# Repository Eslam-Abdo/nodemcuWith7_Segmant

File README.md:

# Basic IoT project using ESP8266 (nodemcu) and microPython
### Requirement: 
change 7-segment's number using (Mobile app or hardware buttons) and display number on both (7-segment and mobile App) in real-time,
there are 3 buttons:
1. Increase
2. Decrease
3. Reset -to reset number to zero-

## project video [*(click here to all videos)*](https://drive.google.com/drive/folders/1r0zepQS2k2B7NYq5-uNhiJdKVNSH9e6j)

## 1. Useful Tutorial
  - [1. Python Tutorial](https://www.w3schools.com/python/default.asp)
  - [2. 30+ MicroPython Projects, Tutorials and Guides with ESP32 / ESP8266](https://randomnerdtutorials.com/projects-esp32-esp8266-micropython/)
  - [3. MicroPython Basics](https://learn.adafruit.com/micropython-basics-what-is-micropython/overview)
  - [4. MicroPython tutorial for ESP8266](https://docs.micropython.org/en/latest/esp8266/tutorial/index.html) *important tutorial*
  - [5. Easy Coding ESP8266 Tutorial *playlist*](https://www.youtube.com/playlist?list=PLfPtpZzK2Z_Qy2ZbbzvWa58cKKOisMUZ1)
  - [6. MicroPython libraries](https://docs.micropython.org/en/latest/library/index.html)

## 2. Getting Started
 - [ 1. Getting started with MicroPython on the ESP8266 *offical site*](https://docs.micropython.org/en/latest/esp8266/tutorial/intro.html#getting-the-firmware)
 - [2. Install uPyCraft IDE : Windows PC Instructions](https://randomnerdtutorials.com/install-upycraft-ide-windows-pc-instructions/)
 - [3. Flash/Upload MicroPython Firmware to ESP32 and ESP8266](https://randomnerdtutorials.com/flash-upload-micropython-firmware-esp32-esp8266/)
 - [4. Getting Started with MicroPython on ESP32 and ESP8266](https://randomnerdtutorials.com/getting-started-micropython-esp32-esp8266/)
 - [5. MicroPython Basics: Load Files & Run Code](https://learn.adafruit.com/micropython-basics-load-files-and-run-code/overview)
  ### How to Load MicroPython on a Board
   - [Serial REPL](https://learn.adafruit.com/micropython-basics-how-to-load-micropython-on-a-board/serial-terminal?view=all#serial-terminal)
   - [ WebREPL](https://learn.adafruit.com/micropython-basics-esp8266-webrepl)
      - [programming page](http://micropython.org/webrepl/)
      - [rebo of webrebl to download page html for use offline](https://github.com/micropython/webrepl)
      - [File Handling using python](https://www.w3schools.com/python/python_file_handling.asp)
      - [Get a list of files with Python 3 (useing listdir in os module you get the files and the folders in the current dir)](https://stackoverflow.com/questions/3207219/how-do-i-list-all-files-of-a-directory)
        ```python
        import os
        arr = os.listdir()
        print(arr)
        ```

## GPIO & 7-Segmant init
- [1. Interacting with GPIOs](https://randomnerdtutorials.com/micropython-gpios-esp32-esp8266/)
- [2. MicroPython: Interrupts with ESP32 and ESP8266](https://randomnerdtutorials.com/micropython-interrupts-esp32-esp8266/)
- [3. Debouncing in interrupt with nodemcu Micropython Steps](https://forum.micropython.org/viewtopic.php?t=1938)
- [4. Delay and timing](https://docs.micropython.org/en/latest/esp8266/quickref.html#delay-and-timing)
- [5. How 7 Segment Displays work](https://randomnerdtutorials.com/circuits-7-segment-displays/)
- [6. Python OOP  - Python Classes and Objects](https://www.w3schools.com/python/python_classes.asp)
- [7. MicroPython Basics: Loading Modules](https://www.digikey.com/en/maker/projects/micropython-basics-loading-modules/9560902ac9654f7e91f098e723d097ad)

## Acess point set up
  - [1. MicroPython: ESP32/ESP8266 Access Point (AP)](https://randomnerdtutorials.com/micropython-esp32-esp8266-access-point-ap/)
  - [2. ESP32/ESP8266 MicroPython Web Server – Control Outputs](https://randomnerdtutorials.com/esp32-esp8266-micropython-web-server/)
  - [3. MicroPython: DS18B20 Temperature Sensor with ESP32 and ESP8266](https://randomnerdtutorials.com/micropython-ds18b20-esp32-esp8266/) 
  - [4.MicroPython: ESP32/ESP8266 with DHT11/DHT22 Web Server (Weather Station))](https://randomnerdtutorials.com/micropython-esp32-esp8266-dht11-dht22-web-server/)
  
## Deep sleep Mode
  - [1. ESP8266 Deep Sleep and Wake Up Sources](https://randomnerdtutorials.com/micropython-esp8266-deep-sleep-wake-up-sources/)
  - [2. Power control *micropython.org*](http://docs.micropython.org/en/v1.9.2/esp8266/esp8266/tutorial/powerctrl.html)
  - [3. ESP8266 Low Power Solutions](https://www.espressif.com/sites/default/files/9b-esp8266-low_power_solutions_en_0.pdf)
  - [4. Low Power Weather Station Datalogger using ESP8266 and BME280 with MicroPython](https://randomnerdtutorials.com/low-power-weather-station-datalogger-using-esp8266-bme280-micropython/)

## MIT App Invertor
  - [1. How to Use MIT App Invertor](https://www.youtube.com/watch?v=qWKcOnoyBzE) 
  - [2. ESP8266 Controlled with Android App (MIT App Inventor)](https://randomnerdtutorials.com/esp8266-controlled-with-android-app-mit-app-inventor/) *using .lua*
  - [3. Build an ESP8266 Web Server – Code and Schematics (NodeMCU)](https://randomnerdtutorials.com/esp8266-web-server/) *using .lua*
  - [4. NodeMcu (ESP8266) Tutorial B-07: Get sensor data from NODEMCU with your Android phone](https://www.youtube.com/watch?v=wwuPzOdqcmY&list=PLfPtpZzK2Z_Qy2ZbbzvWa58cKKOisMUZ1&index=41)
  - [4. Username and Password](https://community.appinventor.mit.edu/t/username-and-password/4499)
  - [5. WiFi Manager Extension **optional**](https://puravidaapps.com/wifi.php)
  - [6. Build an App with App Inventor which can display values of a connected sensor](https://home.et.utwente.nl/slootenvanf/2018/11/22/build-app-inventor-display-connected-sensor/) *important*
  - [7. App Inventor 2 - ESP8266 GPIO Control with Nodemcu LUA](https://www.youtube.com/watch?v=qWKcOnoyBzE)
  - [8. Reading QR code](https://www.youtube.com/watch?v=jIfpHpb4k1k)
  - [9. Using MIT App Inventor Offline](https://www.youtube.com/watch?v=FA4a31Fg2Wo)
  - [10. Progress of App Inventor for iOS](http://doesappinventorrunonios.com)

## ESP8266 Pinouts maping:
```python
D0  = 16
D1  = 5
D2  = 4
D3  = 0
D4  = 2
D5  = 14
D6  = 12
D7  = 13
D8  = 15
D9  = 3
D10 = 1
A0 = 0
```

### *Note*
- Built in Led On Pin D4 So I think it limit in current and the LED is *active LOW*
- PIN D0 is only input without PULL
- you can use Left side pin only as GPIO pins 
- you have only pin A0 as Anlong pin

## ESP8266 Pinouts

## Symbol

## Binary to BCD truth table

##  How to create sockets for server-client interaction

## Differences between 3 Sleep Modes

## MIT App Inventor for iOS

## Pcb Deisgn
### 3D Model [*cleck here to view*](https://a360.co/3qI3qZ3)

### Schmatic digram

### Board

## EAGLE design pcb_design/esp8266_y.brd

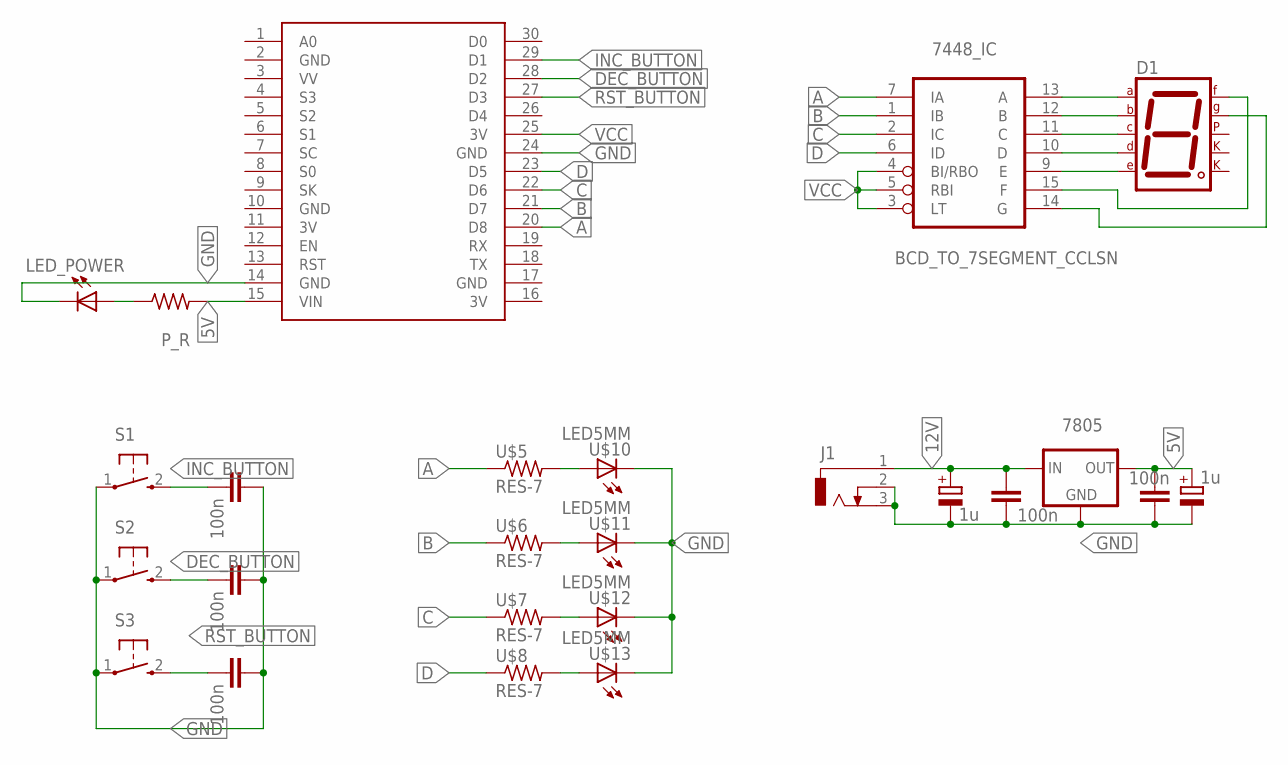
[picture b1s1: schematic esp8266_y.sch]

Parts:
7448_IC: BCD_TO_7SEGMENT_CCLSN; DIL16
7805: 78XXS
D1: 7SEG-CK; 7SEG-13
J1: CON_JACK; DCJ0303
LED_POWER: LED5MM
P_R: RES-7; 0204/7
S1, S2, S3: PUSH_BUTTON; B3F-10XX
U$1: NODEMCU_V3; NODEMCU
U$2, U$3, U$4, U$17, U$18: 100n; C025-025X050
U$5, U$6, U$7, U$8: RES-7; 0204/7
U$10, U$11, U$12, U$13: LED5MM
U$15, U$16: 1u; E3,5-8

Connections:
3V: U$1.11 (3V), U$1.16 (3V)
5V: 7805.OUT, P_R.2, U$1.15 (VIN), U$15.+, U$17.1
12V: 7805.IN, J1.1, U$16.+, U$18.1
A: 7448_IC.7 (IA), U$1.20 (D8), U$5.1
B: 7448_IC.1 (IB), U$1.21 (D7), U$6.1
C: 7448_IC.2 (IC), U$1.22 (D6), U$7.1
D: 7448_IC.6 (ID), U$1.23 (D5), U$8.1
DEC_BUTTON: S2.2 (S), U$1.28 (D2), U$3.2
GND: 7448_IC.8 (GND), 7805.GND, J1.2, J1.3, LED_POWER.K (C), S1.1, S2.1, S3.1, U$1.2 (GND), U$1.10 (GND), U$1.14 (GND), U$1.17 (GND), U$1.24 (GND), U$2.1, U$3.1, U$4.1, U$10.K (C), U$11.K (C), U$12.K (C), U$13.K (C), U$15.-, U$16.-, U$17.2, U$18.2
INC_BUTTON: S1.2 (S), U$1.29 (D1), U$2.2
unnamed: U$5.2, U$10.A
unnamed: LED_POWER.A, P_R.1
unnamed: U$6.2, U$11.A
unnamed: U$7.2, U$12.A
unnamed: U$8.2, U$13.A
unnamed: 7448_IC.11 (C), D1.4 (C)
unnamed: 7448_IC.12 (B), D1.6 (B)
unnamed: 7448_IC.13 (A), D1.7 (A)
unnamed: 7448_IC.10 (D), D1.2 (D)
unnamed: 7448_IC.9 (E), D1.1 (E)
unnamed: 7448_IC.15 (F), D1.9 (F)
unnamed: 7448_IC.14 (G), D1.10 (G)
RST_BUTTON: S3.2 (S), U$1.27 (D3), U$4.2
VCC: 7448_IC.3 (LT), 7448_IC.4 (BI/RBO), 7448_IC.5 (RBI), 7448_IC.16 (VCC), U$1.25 (3V)

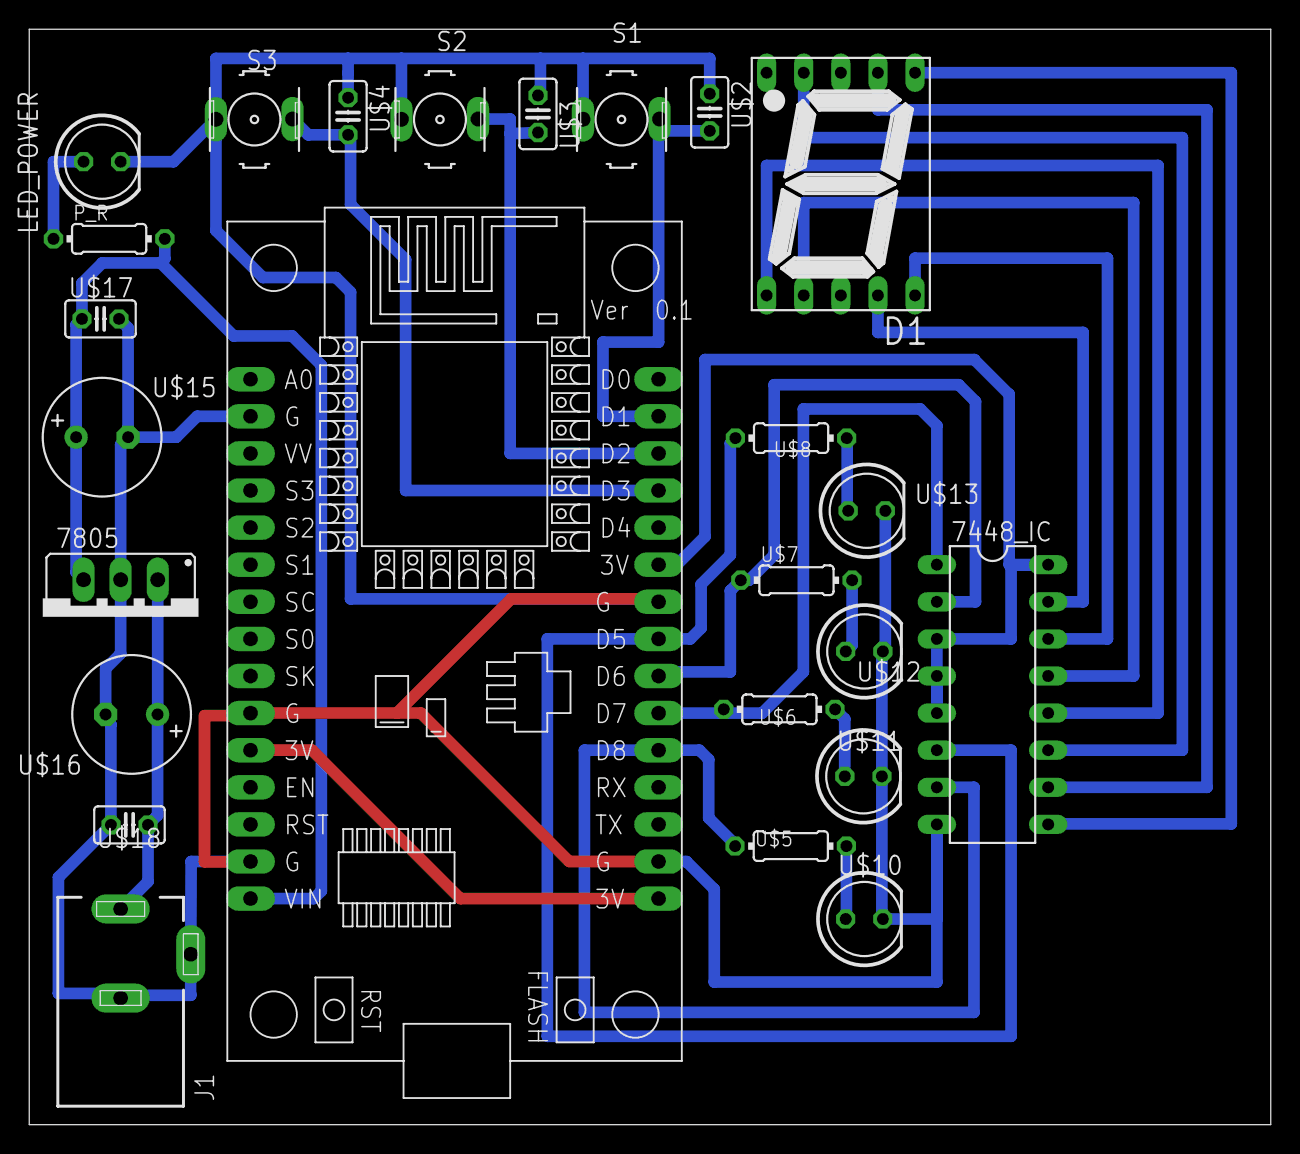
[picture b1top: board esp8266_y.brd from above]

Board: 2 copper layers, 85.0 x 75.0 mm, 25 parts (0 on the bottom side), 24 nets.

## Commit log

2020-12-26 add pinout
2020-12-27 add files
2020-12-30 add to read me
2020-12-31 edit files
2020-12-31 add & update files
2020-12-31 edit name
2021-01-18 add file
2021-01-22 update files
